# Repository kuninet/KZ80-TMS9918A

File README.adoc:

== KZ80シリーズ TMS9918A ビデオボード

=== 概要
* SBC8080バスにつながるTMS9918Aビデオボードのプロジェクトです。
* 本ボードの詳しい説明は以下のwikiページをご覧ください。
** https://github.com/kuninet/KZ80-TMS9918A/wiki

image::image/KZ80-TMS9918A.jpg[]

=== ライセンス
* 本プロジェクトのデータはMITライセンスのもとで公開します。

=== 参考
* 以下のサイトの情報を参考に作成しています。ありがとうございます。
** https://github.com/jblang/TMS9918A
** https://retrobrewcomputers.org/n8vem-pbwiki-archive/0/35845334/48860720/33053543/SRAM%20Replacement%20for%20TMS99x8%20VRAM.pdf

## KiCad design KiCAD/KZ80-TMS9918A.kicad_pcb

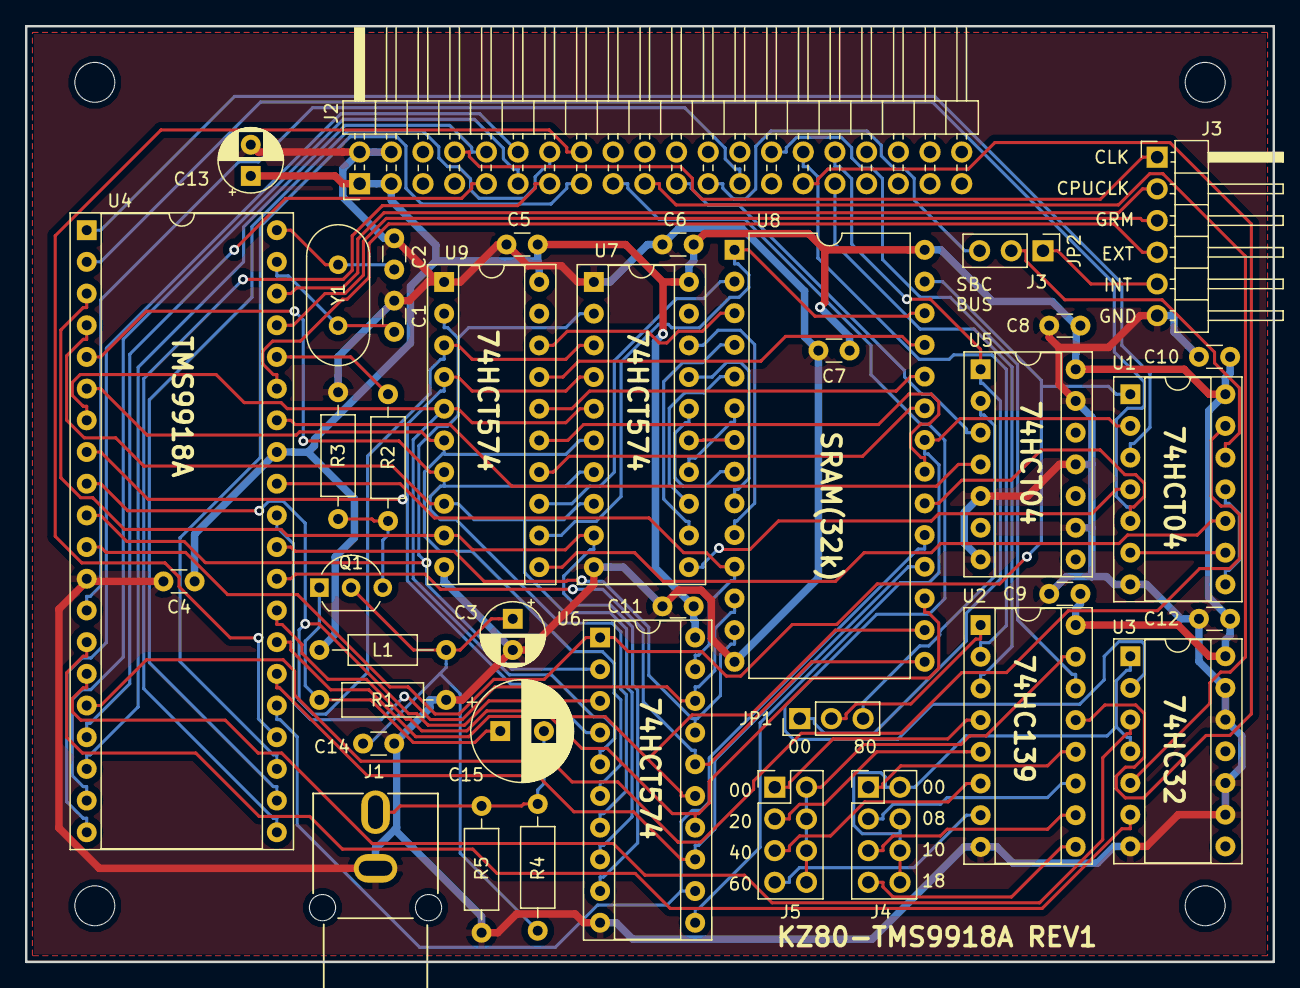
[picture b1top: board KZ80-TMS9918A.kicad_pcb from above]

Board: 2 copper layers, 100.0 x 75.0 mm, 43 parts (0 on the bottom side), 87 nets.

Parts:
C1, C2: 22P; C_Disc_D3.0mm_W1.6mm_P2.50mm
C3, C13: 10u; CP_Radial_D5.0mm_P2.50mm
C4, C5, C6, C7, C8, C9, C10, C11, C12, C14: 0.1u; C_Disc_D3.0mm_W1.6mm_P2.50mm
C15: 470u; CP_Radial_D8.0mm_P3.50mm
J1: Conn_Coaxial; RCAConAE
J2: SBC8080 BUS; PinHeader_2x20_P2.54mm_Horizontal
J3: EXT_JP; PinHeader_1x06_P2.54mm_Horizontal
J4, J5: AD_JP; PinHeader_2x04_P2.54mm_Vertical
JP1: A7_JP; PinHeader_1x03_P2.54mm_Vertical
JP2: INT-J; PinHeader_1x03_P2.54mm_Vertical
L1: L_Core_Ferrite; L_Axial_L5.3mm_D2.2mm_P10.16mm_Horizontal_Vishay_IM-1
MH1, MH2, MH3, MH4: MountingHole; MountingHole_3.2mm_M3
Q1: 2SC1815; TO-92_Inline_Wide
R1: 180; R_Axial_DIN0207_L6.3mm_D2.5mm_P10.16mm_Horizontal
R2: 0; R_Axial_DIN0207_L6.3mm_D2.5mm_P10.16mm_Horizontal
R3: 470; R_Axial_DIN0207_L6.3mm_D2.5mm_P10.16mm_Horizontal
R4: 1k; R_Axial_DIN0207_L6.3mm_D2.5mm_P10.16mm_Horizontal
R5: 2k; R_Axial_DIN0207_L6.3mm_D2.5mm_P10.16mm_Horizontal
U1, U5: 74HCT04; DIP-14_W7.62mm_Socket
U2: 74HC139; DIP-16_W7.62mm_Socket
U3: 74HC32; DIP-14_W7.62mm_Socket
U4: TMS9918A; DIP-40_W15.24mm_Socket
U6, U7, U9: 74HCT574; DIP-20_W7.62mm_Socket
U8: HM62256; DIP-28_W15.24mm
Y1: 10.738635MHZ; Crystal_HC49-U_Vertical

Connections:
/A0: J2.25, U4.13
/A3: J2.28, U2.14
/A4: J2.29, U2.13
/A5: J2.30, U2.2
/A6: J2.31, U2.3
/A7: J2.32, JP1.1, U5.1
/AD0: U4.10, U6.2, U7.2, U9.2
/AD1: U4.9, U6.3, U7.3, U9.3
/AD2: U4.8, U6.4, U7.4, U9.4
/AD3: U4.7, U6.5, U7.5, U9.5
/AD4: U4.6, U6.6, U7.6, U9.6
/AD5: U4.5, U6.7, U7.7, U9.7
/AD6: U4.4, U6.8, U7.8, U9.8
/AD7: U4.3, U6.9, U7.9, U9.9
/CLK: J2.8, J3.1
/COL: U1.10, U9.11
/CPUCLK: J3.2, U4.38
/D0: J2.9, U4.17
/D1: J2.10, U4.18
/D2: J2.11, U4.19
/D3: J2.12, U4.20
/D4: J2.13, U4.21
/D5: J2.14, U4.22
/D6: J2.15, U4.23
/D7: J2.16, U4.24
/EXTVDP: J3.4, U4.35
/GROMCLK: J3.3, U4.37
/INT: J3.5, JP2.1
/INT80: J2.23, JP2.3
/RES: J2.21, U5.3
/ROW: U1.4, U7.11
/R~W: U1.1, U4.11, U6.1, U8.27
/VA0: U7.18, U8.10
/VA1: U7.17, U8.9
/VA2: U7.16, U8.8
/VA3: U7.15, U8.7
/VA4: U7.14, U8.6
/VA5: U7.13, U8.5
/VA6: U7.12, U8.4
/VA7: U8.3, U9.18
/VA8: U8.25, U9.17
/VA9: U8.24, U9.16
/VA10: U8.21, U9.15
/VA11: U8.23, U9.14
/VA12: U8.2, U9.13
/VA13: U8.1, U8.26, U9.12
/VD0: U4.32, U6.19, U8.11
/VD1: U4.31, U6.18, U8.12
/VD2: U4.30, U6.17, U8.13
/VD3: U4.29, U6.16, U8.15
/VD4: U4.28, U6.15, U8.16
/VD5: U4.27, U6.14, U8.17
/VD6: U4.26, U6.13, U8.18
/VD7: U4.25, U6.12, U8.19
/~CAS: U1.5, U4.2, U8.20
/~CSR: U3.3, U4.15
/~CSW: U3.6, U4.14
/~INT: U1.13, U4.16
/~IOR: J2.17, U3.2
/~IOW: J2.19, U3.5
/~RAS: U1.3, U4.1
/~RES: U4.34, U5.4
/~R~W: U1.2, U6.11, U8.22
GND: C1.2, C2.2, C3.2, C4.2, C5.2, C6.2, C7.2, C8.2, C9.2, C10.2, C11.2, C12.2, C13.2, C14.2, J1.2, J2.2, J2.4, J3.6, R1.2, R3.2, R5.2, U1.7, U2.8, U3.7, U3.9, U3.10, U3.12, U3.13, U4.12, U5.5, U5.7, U5.9, U5.11, U5.13, U6.10, U7.1, U7.10, U8.14, U9.1, U9.10
unnamed: C1.1, U4.39, Y1.1
unnamed: C2.1, U4.40, Y1.2
unnamed: C3.1, C14.1, L1.2, Q1.2, R4.1
unnamed: C15.1, Q1.1, R1.1
unnamed: C15.2, J1.1, R4.2, R5.1
unnamed: J4.1, U2.12
unnamed: J4.2, J4.4, J4.6, J4.8, U3.1, U3.4
unnamed: J4.3, U2.11
unnamed: J4.5, U2.10
unnamed: J4.7, U2.9
unnamed: J5.1, U2.4
unnamed: J5.2, J5.4, J5.6, J5.8, U2.15
unnamed: J5.3, U2.5
unnamed: J5.5, U2.6
unnamed: J5.7, U2.7
unnamed: JP1.2, U2.1
unnamed: JP1.3, U5.2
unnamed: JP2.2, U1.12
unnamed: Q1.3, R2.2, R3.1
unnamed: R2.1, U4.36
unnamed: U1.6, U1.9
unnamed: U1.8, U1.11
VCC: C4.1, C5.1, C6.1, C7.1, C8.1, C9.1, C10.1, C11.1, C12.1, C13.1, J2.1, J2.3, L1.1, U1.14, U2.16, U3.14, U4.33, U5.14, U6.20, U7.20, U8.28, U9.20

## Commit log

2019-06-11 init commit
2019-06-11 Create LICENSE
2019-06-11 回路図イメージファイル追加
2019-07-15 RCAコネクタフットプリント作成。出力回路見直し
2019-07-15 改良版回路図再出力
2019-07-15 回路図表記間違い修正 74HC574→74HCT574
2019-07-15 ガーバーデータ出力
2019-07-16 パターンチェック後 SBCバスINT修正 、製造ファイル再出力
2019-07-16 回路図 修正版 再出力
2019-08-10 回路見直し&パターン再作成
2019-08-10 回路図イメージデータ最新化
2019-09-02 INT端子ジャンパ装備 パターン再作成、ガーバー出力
2019-09-07 ガーバーデータ出力設定見直し。プロットし直し
2021-11-23 回路図イメージ差し替え
